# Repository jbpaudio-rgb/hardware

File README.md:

# Octavio Synth — synthé matériel

Un synthé de table à 4 parties : Raspberry Pi 5, carte HAT audio, façade RP2040 (9 encodeurs, 14 boutons, LED), écran tactile 5 po, boîtier imprimé en 3D. Il fait tourner les moteurs des plugins Octavio (MINI, PRO70, A26, J8, CS8, VC3, M20, EASEL, VACT), plus DX7, DFAM, DR8, SAMPLER et LINE IN.

## Où trouver quoi

| Dossier | Contenu |
| --- | --- |
| `box/cartes/facade` | Carte de façade (KiCad), Gerbers, BOM et CPL pour JLCPCB : `octavio-facade-gerbers-jlcpcb.zip`, `jlcpcb-bom.csv`, `jlcpcb-cpl.csv` |
| `box/cartes/hat` | Carte HAT audio (KiCad), Gerbers, BOM et CPL pour JLCPCB |
| `box/enclosure` | Boîtier : fichiers STL à imprimer, guide de montage 3D (`guide-montage.html`), aperçu 3D, liste de quincaillerie (`LISEZMOI.md`) |
| `box/facade-fw` | Micrologiciel du RP2040 de la façade |
| `box/systeme` | Installation sur le Pi : services, transfert de fichiers par USB-C |
| `box/web` | Simulateur dans le navigateur (`octavio-box.html`) |
| `box/` | Le programme du synthé (C++) : `Box.h`, `Panel.h`, `ui/`, `main.cpp` |
| `core/` | Les moteurs de son et les effets, partagés avec les plugins |

Le détail du programme est dans [`box/README.md`](box/README.md).

## Compiler

```
cmake -S box -B build -DCMAKE_BUILD_TYPE=Release
cmake --build build -j
```

Sur le Raspberry Pi, il faut ALSA et SDL2 (`sudo apt install libasound2-dev libsdl2-dev`). Sans carte son ni écran : `-DOCTAVIO_NO_DEVICES=ON`.

Le simulateur : `WASI_SDK=/chemin/vers/wasi-sdk bash box/web/build.sh`.

## Commander les cartes

Dans chaque dossier de carte : le zip de Gerbers, `jlcpcb-bom.csv` et `jlcpcb-cpl.csv`. Chez JLCPCB : 4 couches, 1,6 mm, assemblage Standard côté Top. Les étapes sont dans le `LISEZMOI.md` de chaque carte.

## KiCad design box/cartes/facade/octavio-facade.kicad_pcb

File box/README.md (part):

# Octavio Box

The program of the Octavio hardware synth: a 4-part multitimbral synth. Each part has one of the 11 Octavio engines
(`core/synth`), its own 8-slot FX rack (`core/FxEngine.h`) and its own MIDI channel; plus a mixer, MIDI in and a
shared tempo. It uses the plugins' C++ engines
as they are (no JUCE), with [RtAudio](https://github.com/thestk/rtaudio) and [RtMidi](https://github.com/thestk/rtmidi)
for the audio and MIDI devices (`third_party/`, MIT-style licences).

It runs the same on a Mac (to try it now) and on a Raspberry Pi 5 / CM5 (the hardware). Until the front panel exists,
it is driven by commands typed in the terminal; the panel will send the same commands.

## Build and run

Mac (needs the Xcode command line tools and CMake: `xcode-select --install`, `brew install cmake`):

```
cmake -S box -B build-box
cmake --build build-box
./build-box/octavio-box
```

Raspberry Pi OS: `sudo apt install cmake g++ libasound2-dev`, then the same three lines. Or all at once (packages, code in `~/hardware`, build, screen lines in `config.txt`, services that start at power-on): `curl -sL https://raw.githubusercontent.com/jbpaudio-rgb/hardware/main/box/systeme/installer.sh | bash`, then `sudo reboot`.

Options: `--buffer 128` (samples per block), `--rate 48000`, `--device n` (see `devices`), `--script file`
(commands run at start, for example a saved state).

## Playing it

- Parts start as MINI, PRO70, VACT and DR8 on MIDI channels 1-4. `chan` changes a part's channel; two parts on the
  same channel play together (a layer). A channel no part listens to plays the selected part.
- Every MIDI input and output is opened (looked for again every 2 s), plus virtual ports "Octavio Box" for a DAW. A port
  named after a Bluetooth device BlueZ knows (`bluetoothctl devices`) counts as Bluetooth (BLE MIDI: BlueZ built with
  MIDI support), the others as USB.
- CCs follow the plugin and the app: each engine's controls on CC 2-5, 7-31, 70-95, 102-119, 33-63 (see `params`).
  Any control (and any switch) can be given a CC by MIDI learn: a long press on it on the screen, then move a knob of
  the MIDI controller (on the part's channel). A learnt CC goes before the default one; it is saved in the multi
  (`cc <n> <engine> <control>`), and the screen shows it under the control.
- Tempo and sync (TEMPO & SYNC page, or `sync`): the clock is internal or follows MIDI clock from DIN MIDI, USB or
  Bluetooth; start / stop received or not; MIDI clock (and start / stop) sent to DIN, USB and / or Bluetooth; DIN MIDI
  thru on or off; a multi loads its tempo or not. Kept in `~/octavio/reglages.txt`.
- Type `help` for the commands. Example:

```
p 2              part 2
eng cs8          CS8 on it
params cutoff    its controls whose name has CUTOFF
set cutoff 0.7
fx slot          the FX slots
fxset slot0 7    reverb in slot 1 (0 = off, 1-16 = OVERDRIVE ... SHIMMER)
note 60 .8 500   play a note
bpm 100
play
status           engines, levels, CPU
chan 5           part 2 now listens to MIDI channel 5
savepart pad.txt this part's sound (p 4, then load pad.txt, copies it to part 4)
save live.txt    all 4 parts, as commands (load live.txt or --script live.txt)
```

## The screen

`ui/Screen.h` draws the synth's screen (Raspberry Pi Touch Display 2, 5", used in landscape: 1280 x 720), in a sober
hardware style: the page's title at the top, in the selected part's colour (the 1-4 buttons change the part), with
in its right corner the output's waveform (tap it: a tuner for the selected part), the tempo with its clock source
(tap it: TEMPO & SYNC) and a play / stop button; then the page chosen with the panel's page buttons. The 8 controls of a page sit 2 x 4 like the 8 encoders to
the right of the screen, each with a ring like the encoder's LED ring; a control that just moved lights up in the part's
colour. The pages are described below (front panel).

Touch: tap a part to select it, drag a control up or down to change it (double-tap = default value), tap the play button
to start / stop, on PRESETS (MIXER's tabs) tap a sound or a multi to pick it and tap it again to load it. The screen goes through the same logic as
the front panel (`Panel.h`), so the knobs, the buttons and the touch screen always agree.

It is drawn in software (`ui/Canvas.h`, about 2 ms per picture on a desktop CPU) and shown:
- on the Pi, straight on the display through KMS (no desktop needed): `--rotate 90` or `--rotate 270` turns the
  picture for the portrait panel (try the other one if it is upside down); the touch panel is read from `/dev/input`.
  `config.txt` needs `dtoverlay=vc4-kms-v3d` and `dtoverlay=vc4-kms-dsi-ili9881-5inch`; the user running octavio-box
  needs the `video` and `input` groups;
- on a computer, in a window when SDL2 is installed (`brew install sdl2`, `apt install libsdl2-dev`), `--zoom 0.75`
  for a smaller window. Keys stand in for the panel: 1-4 parts, `e v b f t m q x i p` pages, `[` `]` knob 9, space play.

`--no-screen` runs without it; `shot file.png` saves a picture of it (also in `--render`, for tests), `touch x y dy`
plays a finger, `page`, `knob` and `push` play the front panel from the terminal. With a screen, the synth keeps running
when the terminal closes (as a service). Fonts: DejaVu Sans Condensed (`third_party/fonts`, free licence).

## In a web browser

`box/web/` builds the same program for the browser (`WASI_SDK=/path/to/wasi-sdk box/web/build.sh`): the synth, the
panel's logic and the screen are compiled to WebAssembly (`boxwasm.cpp`) and `octavio-box.html` is one self-contained
page with the front panel around the screen. The sound runs in an AudioWorklet; the page keeps a copy of the synth for
the panel and the screen and posts each change to it. The virtual panel speaks the real panel's USB-MIDI protocol and
lights its rings the way the panel firmware does. Encoders: drag or wheel, click = push. Notes: the computer keyboard,
the keys under the panel or any Web MIDI input. Multis are kept in the browser.

## Offline render (no devices)

`octavio-box --render out.wav < script.txt` runs the commands of a script, where `wait <ms>` renders that much sound,
and writes a WAV. Build it alone with `-DOCTAVIO_NO_DEVICES=ON` (no audio library needed).

## Measured load

On one core of an Intel Xeon at 2.1 GHz (test server): 4 parts (J8, PRO70 and CS8 replaying 6-note chords, DR8
playing), each with 8 effects (reverb, shimmer, granular, delay, phaser, chorus, tape, overdrive) = about 29 % of one
core, 16 MB of memory. To be measured again on a Raspberry Pi 5.

## On the hardware synth (Raspberry Pi 5 + Octavio HAT + front panel)
`/boot/firmware/config.txt`:
```
dtoverlay=hifiberry-dacplusadcpro
dtoverlay=uart2-pi5
```
Then `octavio-box --device <n>` with the HiFiBerry card (see `devices`). On start it also:
- opens DIN MIDI on `/dev/ttyAMA2` at 31250 baud (`--serial` to change). MIDI IN plays like any other input; everything is echoed to MIDI OUT (thru);
- switches the headphone amplifier on (`--phones 0-63`, default 48; `phones` command while running);
- looks for the front panel ("Octavio Facade" USB-MIDI) every 2 s, so it can be plugged in at any time.

Files over USB (`systeme/`): `sudo sh systeme/usb-gadget.sh` once makes the Pi 5's USB-C port a USB device when a
computer is plugged into it (an Ethernet gadget; the box is 10.55.0.1 and `octavio.local`) and starts
`systeme/transfert.py`, a page at http://octavio.local: the multis (download one or all as a zip, upload, delete) and
the SAMPLER's WAV files (drag and drop files or whole folders, download, delete), straight on the SD card; the box
sees them at once. It answers only on the USB link. The screen says when a computer is connected. The computer then
powers the box through that port: it must give 3 A (most laptops' USB-C ports do), or a powered USB-C hub goes
between them. Adjust the user and paths in `systeme/octavio-transfert.service` if the box's user is not `octavio`.

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
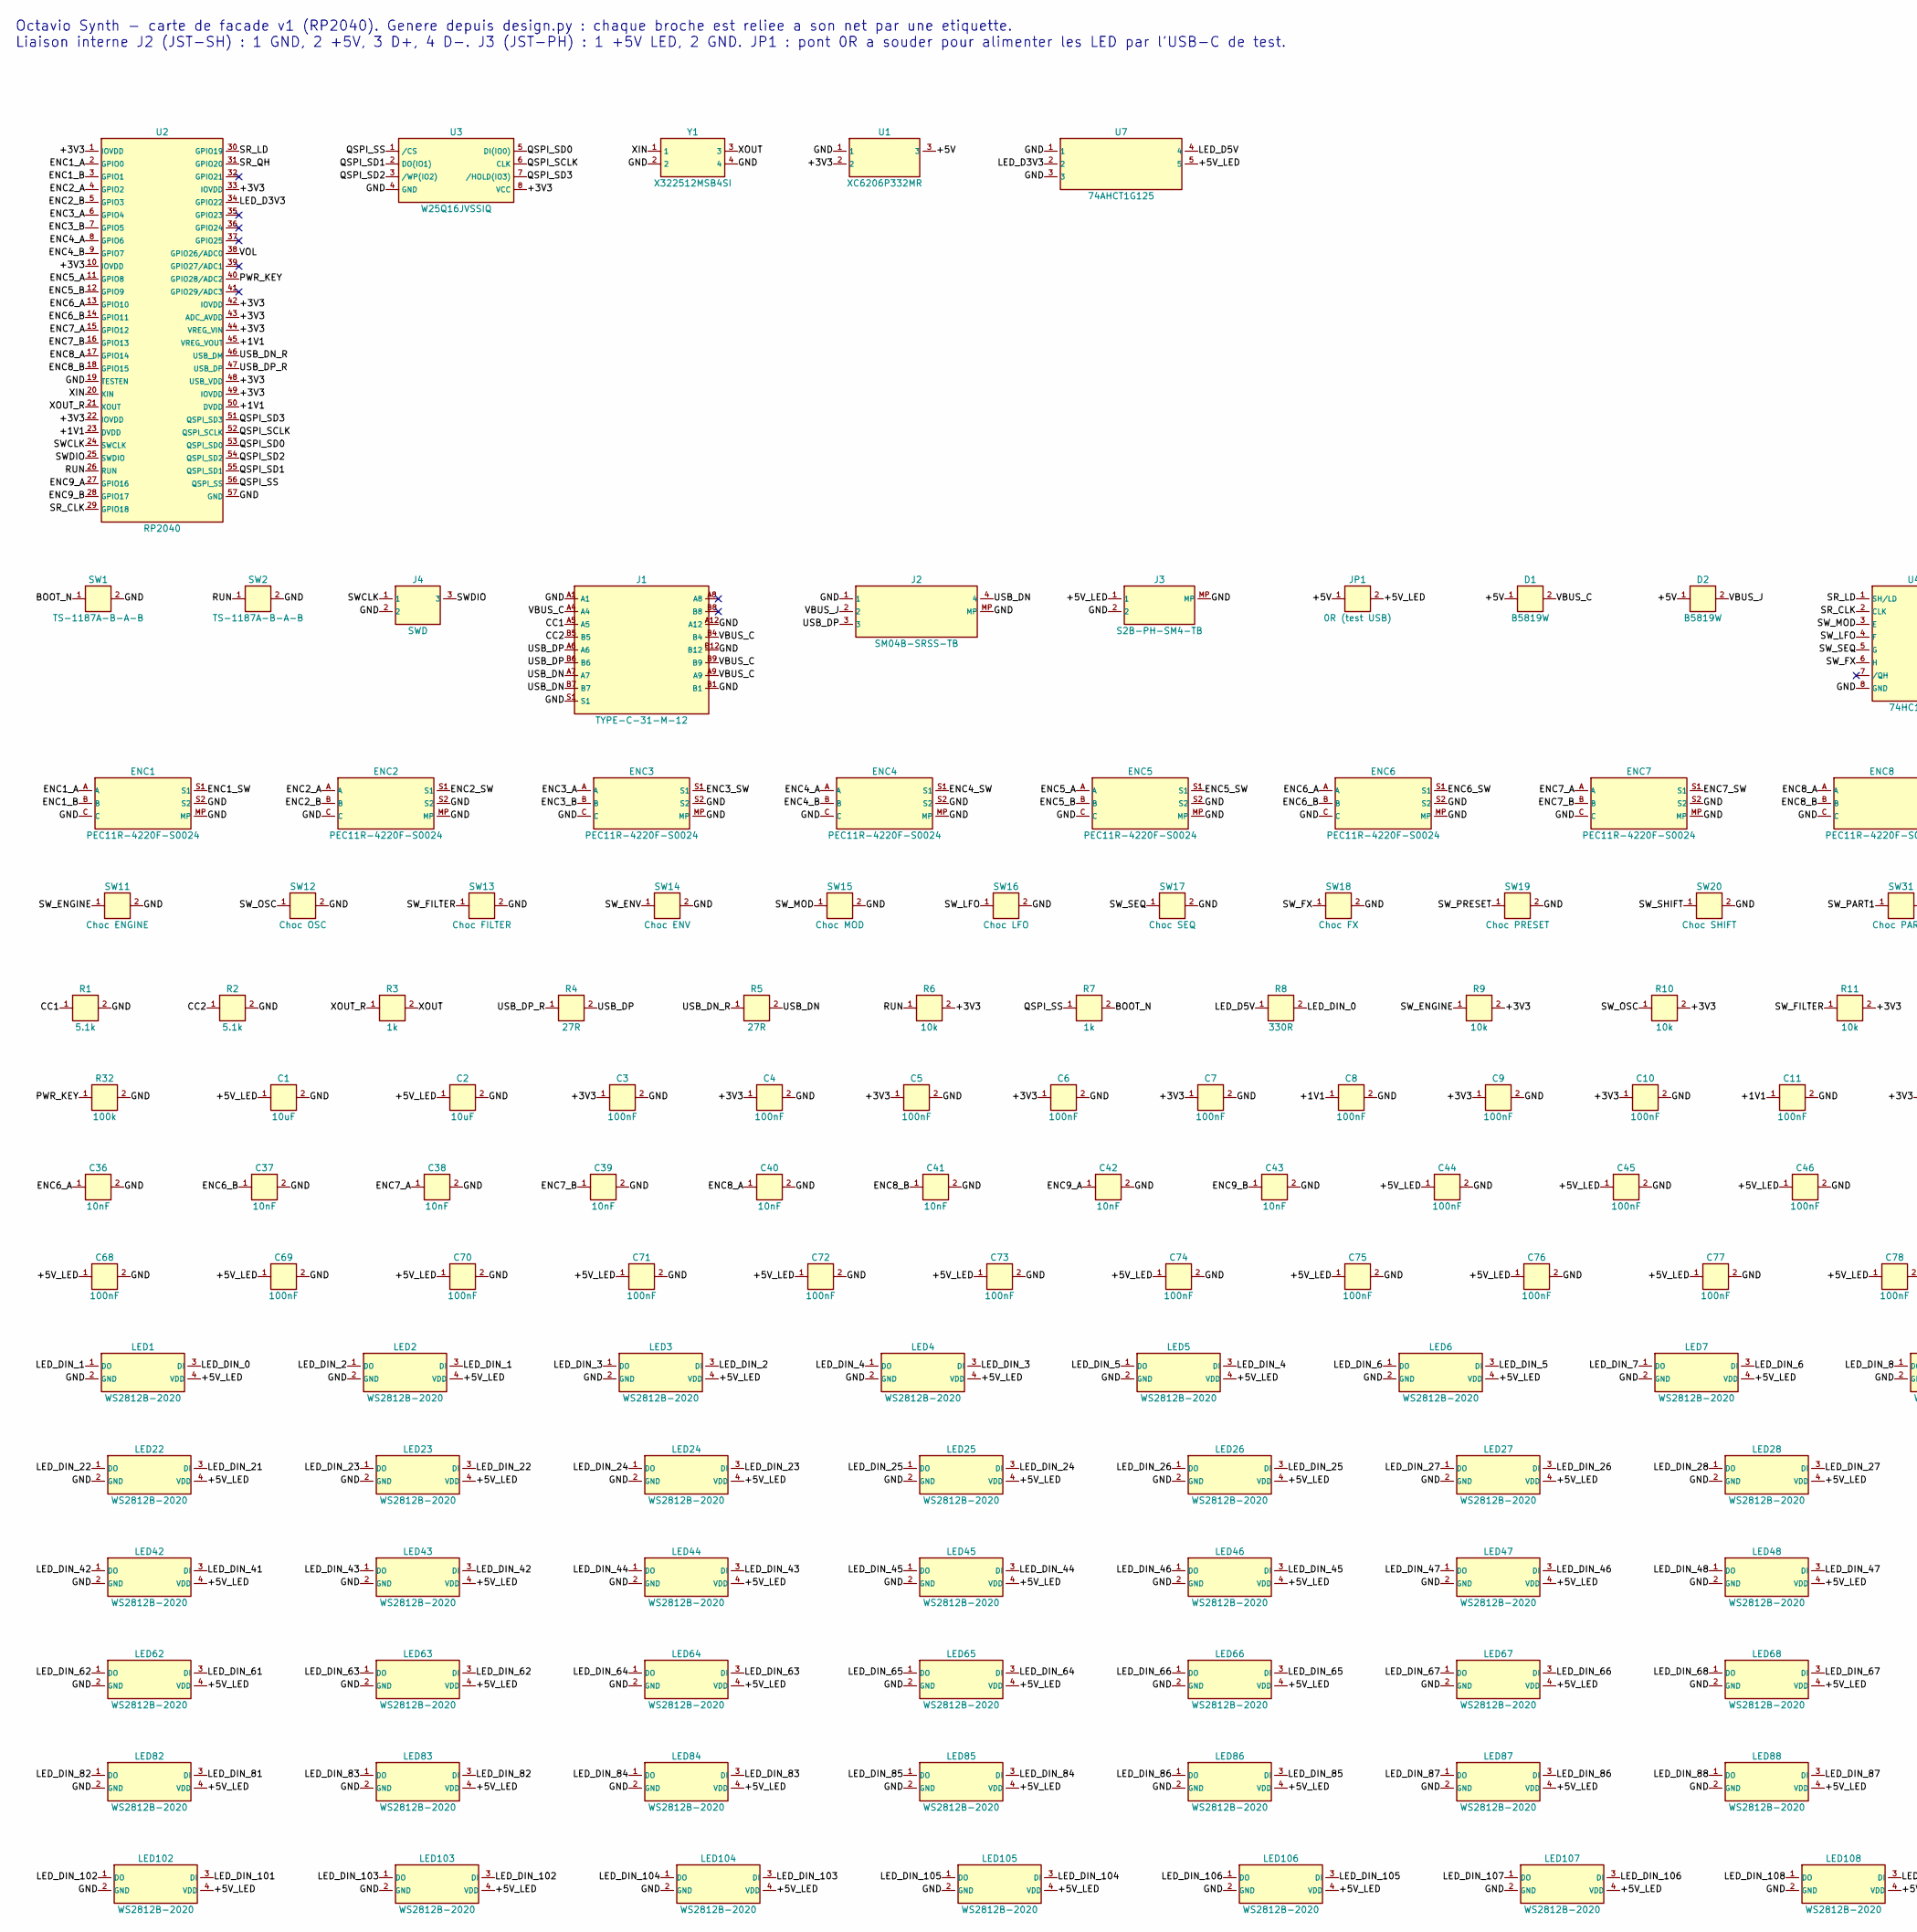
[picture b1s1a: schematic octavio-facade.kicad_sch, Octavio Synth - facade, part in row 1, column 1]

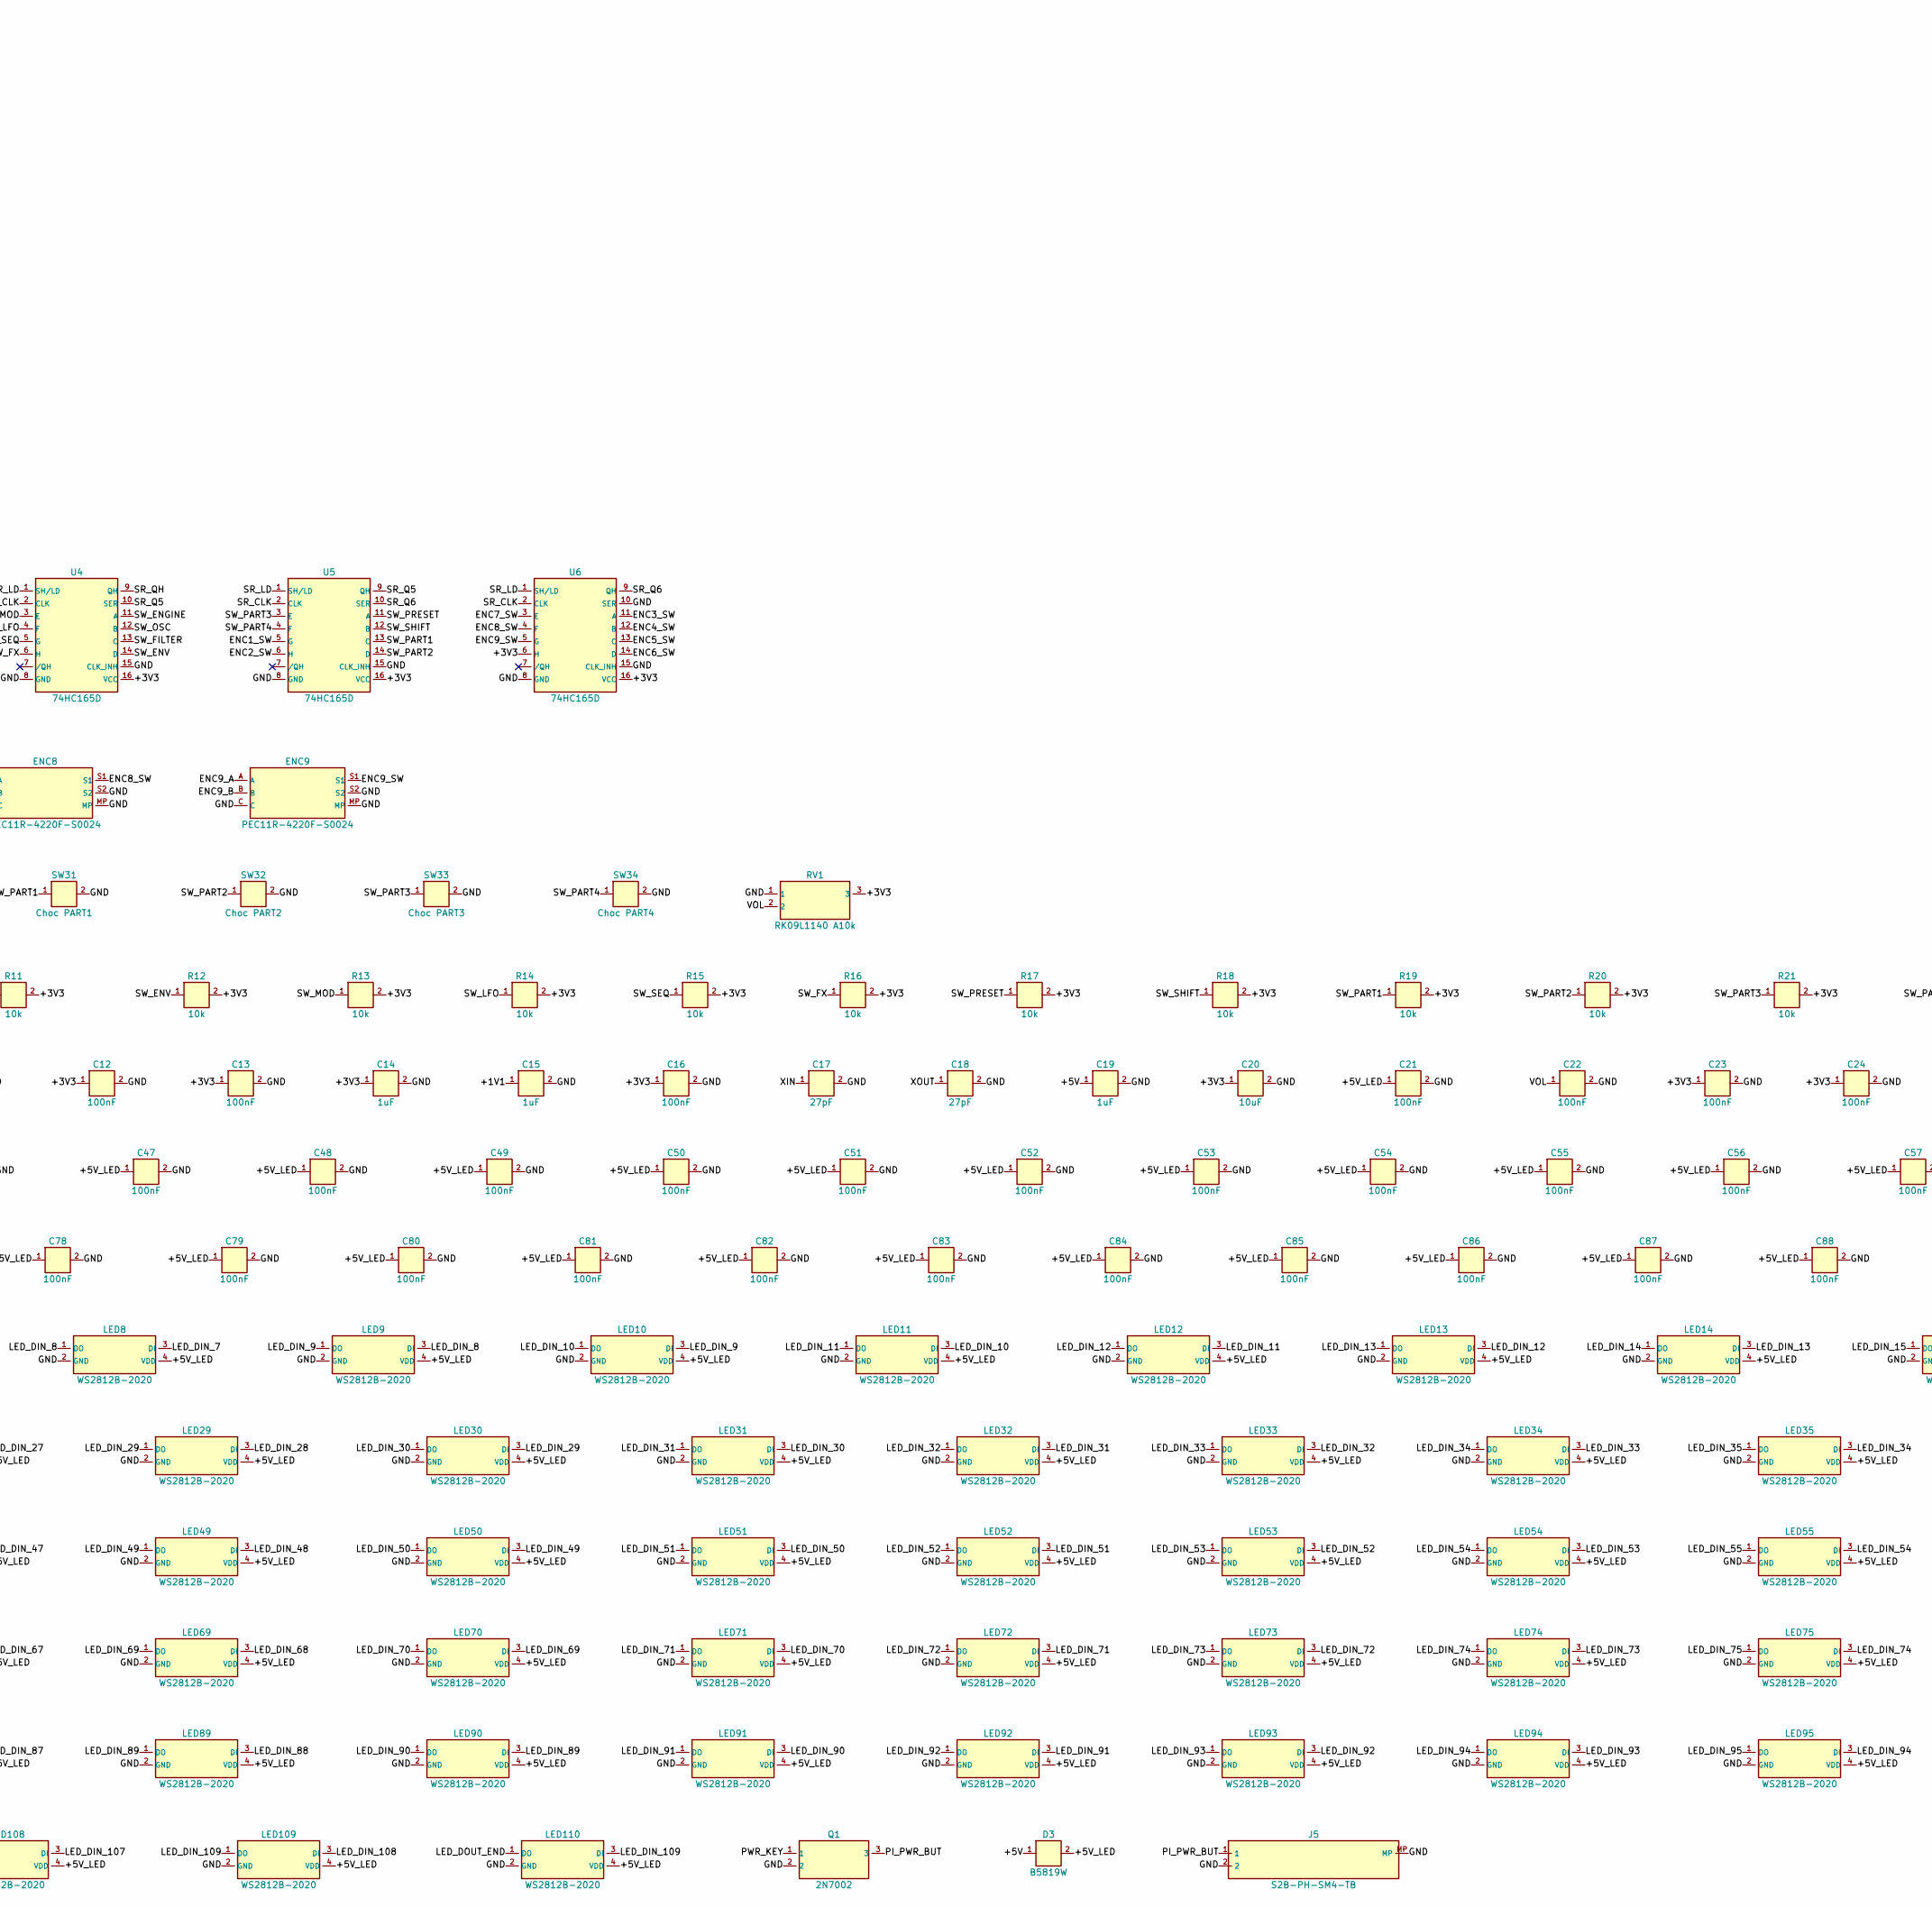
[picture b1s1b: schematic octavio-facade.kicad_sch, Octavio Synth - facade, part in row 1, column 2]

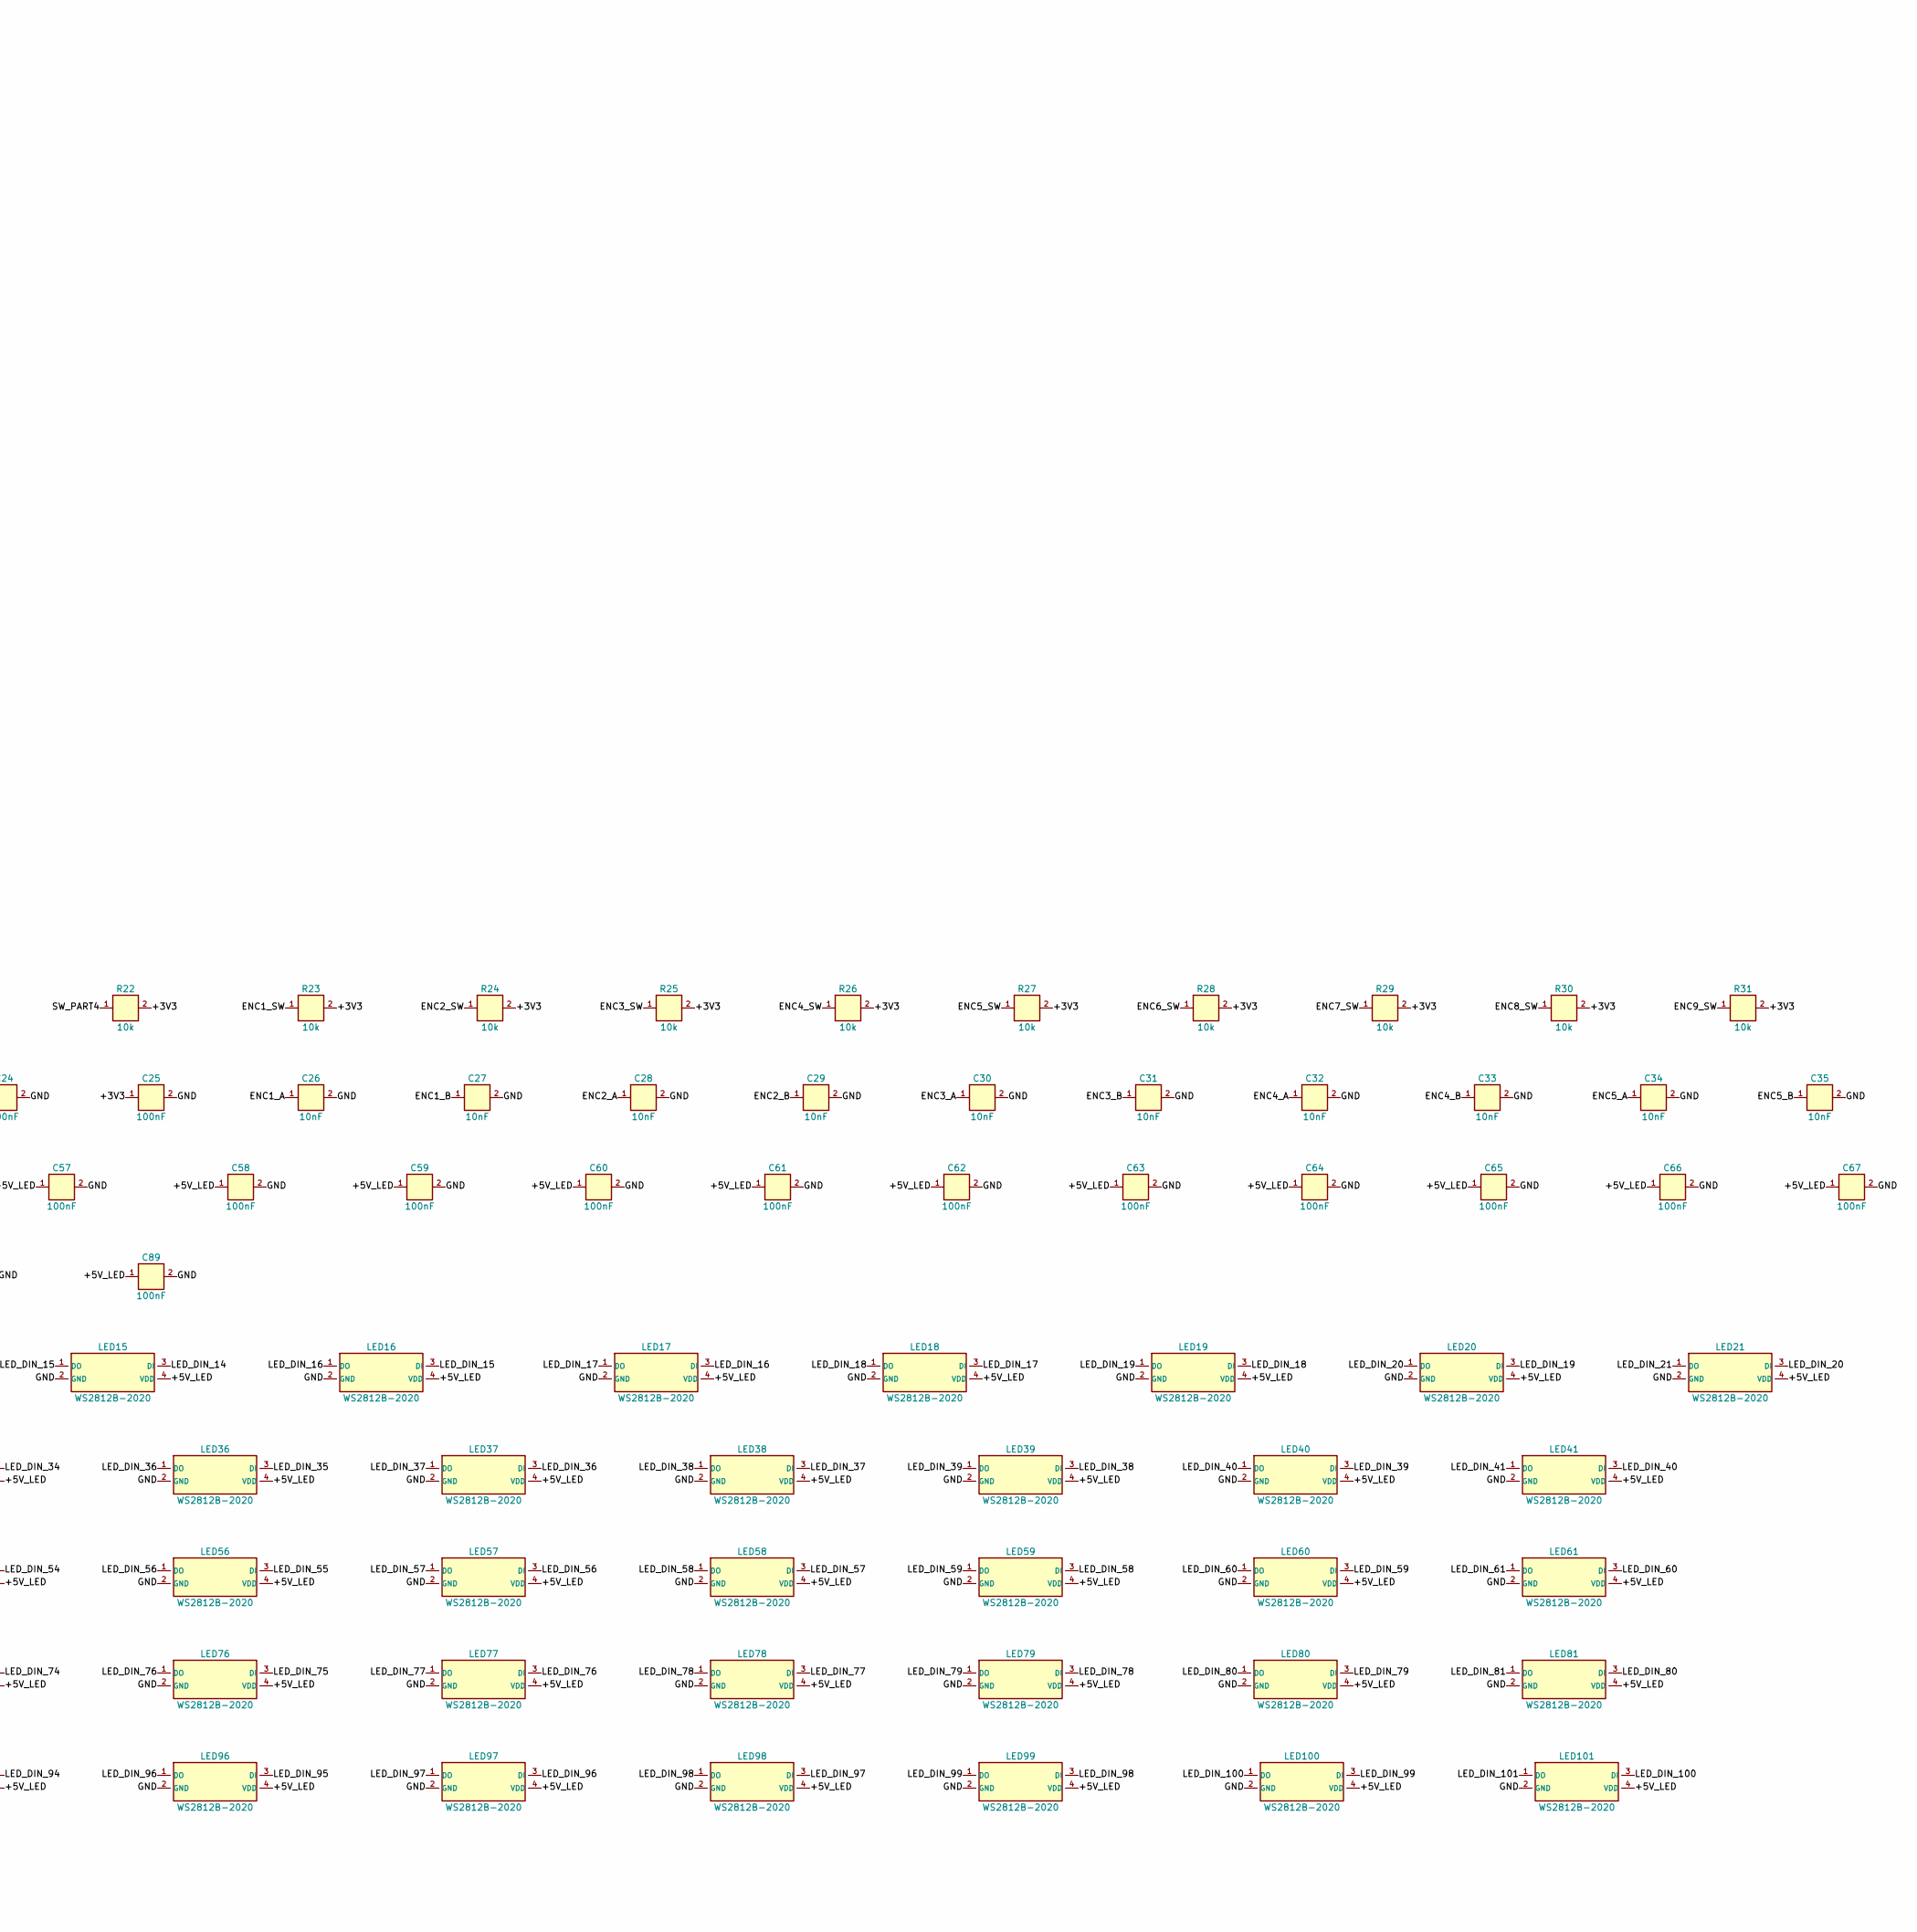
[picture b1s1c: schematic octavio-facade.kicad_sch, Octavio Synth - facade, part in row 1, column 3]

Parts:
C1, C2, C20: 10uF; C_0603_1608Metric; LCSC C19702
C3, C4, C5, C6, C7, C8, C9, C10, C11, C12, C13, C16, C21, C22, C23, C24, C25, C44, C45, C46, C47, C48, C49, C50, C51, C52, C53, C54, C55, C56, C57, C58, C59, C60, C61, C62, C63, C64, C65, C66, C67, C68, C69, C70, C71, C72, C73, C74, C75, C76, C77, C78, C79, C80, C81, C82, C83, C84, C85, C86, C87, C88, C89: 100nF; C_0402_1005Metric; LCSC C1525
C14, C15, C19: 1uF; C_0402_1005Metric; LCSC C52923
C17, C18: 27pF; C_0402_1005Metric; LCSC C1557
C26, C27, C28, C29, C30, C31, C32, C33, C34, C35, C36, C37, C38, C39, C40, C41, C42, C43: 10nF; C_0402_1005Metric; LCSC C15195
D1, D2, D3: B5819W; D_SOD-123; LCSC C8598
ENC1, ENC2, ENC3, ENC4, ENC5, ENC6, ENC7, ENC8, ENC9: PEC11R-4220F-S0024; RotaryEncoder_Alps_EC11E-Switch_Vertical_H20mm; LCSC C143797
J1: TYPE-C-31-M-12; USB_C_Receptacle_HRO_TYPE-C-31-M-12; LCSC C165948
J2: SM04B-SRSS-TB; JST_SH_SM04B-SRSS-TB_1x04-1MP_P1.00mm_Horizontal; LCSC C160404
J3, J5: S2B-PH-SM4-TB; JST_PH_S2B-PH-SM4-TB_1x02-1MP_P2.00mm_Horizontal; LCSC C295747
J4: SWD; PinHeader_1x03_P2.54mm_Vertical
JP1: 0R (test USB); R_0603_1608Metric
LED1, LED2, LED3, LED4, LED5, LED6, LED7, LED8, LED9, LED10, LED11, LED12, LED13, LED14, LED15, LED16, LED17, LED18, LED19, LED20, LED21, LED22, LED23, LED24, LED25, LED26, LED27, LED28, LED29, LED30, LED31, LED32, LED33, LED34, LED35, LED36, LED37, LED38, LED39, LED40, LED41, LED42, LED43, LED44, LED45, LED46, LED47, LED48, LED49, LED50, LED51, LED52, LED53, LED54, LED55, LED56, LED57, LED58, LED59, LED60, LED61, LED62, LED63, LED64, LED65, LED66, LED67, LED68, LED69, LED70, LED71, LED72, LED73, LED74, LED75, LED76, LED77, LED78, LED79, LED80, LED81, LED82, LED83, LED84, LED85, LED86, LED87, LED88, LED89, LED90, LED91, LED92, LED93, LED94, LED95, LED96, LED97, LED98, LED99, LED100, LED101, LED102, LED103, LED104, LED105, LED106, LED107, LED108, LED109, LED110: WS2812B-2020; LED_WS2812B-2020; LCSC C965555
Q1: 2N7002; SOT-23; LCSC C8545
R1, R2: 5.1k; R_0402_1005Metric; LCSC C25905
R3, R7: 1k; R_0402_1005Metric; LCSC C11702
R4, R5: 27R; R_0402_1005Metric; LCSC C25100
R6, R9, R10, R11, R12, R13, R14, R15, R16, R17, R18, R19, R20, R21, R22, R23, R24, R25, R26, R27, R28, R29, R30, R31: 10k; R_0402_1005Metric; LCSC C25744
R8: 330R; R_0402_1005Metric; LCSC C25104
R32: 100k; R_0402_1005Metric; LCSC C25741
RV1: RK09L1140 A10k; Potentiometer_Alps_RK09L_Single_Vertical; LCSC C470448
SW1, SW2: TS-1187A-B-A-B; SW_SPST_SKQG_WithoutStem; LCSC C318884
SW11: Choc ENGINE; SW_Kailh_Choc_V1_1.00u; LCSC C400229
SW12: Choc OSC; SW_Kailh_Choc_V1_1.00u; LCSC C400229
SW13: Choc FILTER; SW_Kailh_Choc_V1_1.00u; LCSC C400229
SW14: Choc ENV; SW_Kailh_Choc_V1_1.00u; LCSC C400229
SW15: Choc MOD; SW_Kailh_Choc_V1_1.00u; LCSC C400229
SW16: Choc LFO; SW_Kailh_Choc_V1_1.00u; LCSC C400229
SW17: Choc SEQ; SW_Kailh_Choc_V1_1.00u; LCSC C400229
SW18: Choc FX; SW_Kailh_Choc_V1_1.00u; LCSC C400229
SW19: Choc PRESET; SW_Kailh_Choc_V1_1.00u; LCSC C400229
SW20: Choc SHIFT; SW_Kailh_Choc_V1_1.00u; LCSC C400229
SW31: Choc PART1; SW_Kailh_Choc_V1_1.00u; LCSC C400229
SW32: Choc PART2; SW_Kailh_Choc_V1_1.00u; LCSC C400229
SW33: Choc PART3; SW_Kailh_Choc_V1_1.00u; LCSC C400229
SW34: Choc PART4; SW_Kailh_Choc_V1_1.00u; LCSC C400229
U1: XC6206P332MR; SOT-23; LCSC C5446
U2: RP2040; RP2040-QFN-56; LCSC C2040
U3: W25Q16JVSSIQ; SOIC-8_5.23x5.23mm_P1.27mm; LCSC C131025
U4, U5, U6: 74HC165D; SOIC-16_3.9x9.9mm_P1.27mm; LCSC C5613
U7: 74AHCT1G125; SOT-353_SC-70-5; LCSC C12495
Y1: X322512MSB4SI; Crystal_SMD_3225-4Pin_3.2x2.5mm; LCSC C9002

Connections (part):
+1V1: C8.1, C11.1, C15.1, U2.23 (DVDD), U2.45 (VREG_VOUT), U2.50 (DVDD)
+3V3: C3.1, C4.1, C5.1, C6.1, C7.1, C9.1, C10.1, C12.1, C13.1, C14.1, C16.1, C20.1, C23.1, C24.1, C25.1, R6.2, R9.2, R10.2, R11.2, R12.2, R13.2, R14.2, R15.2, R16.2, R17.2, R18.2, R19.2, R20.2, R21.2, R22.2, R23.2, R24.2, R25.2, R26.2, R27.2, R28.2, R29.2, R30.2, R31.2, RV1.3, U1.2, U2.1 (IOVDD), U2.10 (IOVDD), U2.22 (IOVDD), U2.33 (IOVDD), U2.42 (IOVDD), U2.43 (ADC_AVDD), U2.44 (VREG_VIN), U2.48 (USB_VDD), U2.49 (IOVDD), U3.8 (VCC), U4.16 (VCC), U5.16 (VCC), U6.6 (H), U6.16 (VCC)
+5V: C19.1, D1.1, D2.1, D3.1, JP1.1, U1.3
+5V_LED: C1.1, C2.1, C21.1, C44.1, C45.1, C46.1, C47.1, C48.1, C49.1, C50.1, C51.1, C52.1, C53.1, C54.1, C55.1, C56.1, C57.1, C58.1, C59.1, C60.1, C61.1, C62.1, C63.1, C64.1, C65.1, C66.1, C67.1, C68.1, C69.1, C70.1, C71.1, C72.1, C73.1, C74.1, C75.1, C76.1, C77.1, C78.1, C79.1, C80.1, C81.1, C82.1, C83.1, C84.1, C85.1, C86.1, C87.1, C88.1, C89.1, D3.2, J3.1, JP1.2, LED1.4 (VDD), LED2.4 (VDD), LED3.4 (VDD), LED4.4 (VDD), LED5.4 (VDD), LED6.4 (VDD), LED7.4 (VDD), LED8.4 (VDD), LED9.4 (VDD), LED10.4 (VDD), LED11.4 (VDD), LED12.4 (VDD), LED13.4 (VDD), LED14.4 (VDD), LED15.4 (VDD), LED16.4 (VDD), LED17.4 (VDD), LED18.4 (VDD), LED19.4 (VDD), LED20.4 (VDD), LED21.4 (VDD), LED22.4 (VDD), LED23.4 (VDD), LED24.4 (VDD), LED25.4 (VDD), LED26.4 (VDD), LED27.4 (VDD), LED28.4 (VDD)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
BOOT_N: R7.2, SW1.1
CC1: J1.A5, R1.1
CC2: J1.B5, R2.1
ENC1_A: C26.1, ENC1.A, U2.2 (GPIO0)
ENC1_B: C27.1, ENC1.B, U2.3 (GPIO1)
ENC1_SW: ENC1.S1, R23.1, U5.5 (G)
ENC2_A: C28.1, ENC2.A, U2.4 (GPIO2)
ENC2_B: C29.1, ENC2.B, U2.5 (GPIO3)
ENC2_SW: ENC2.S1, R24.1, U5.6 (H)
ENC3_A: C30.1, ENC3.A, U2.6 (GPIO4)
ENC3_B: C31.1, ENC3.B, U2.7 (GPIO5)
ENC3_SW: ENC3.S1, R25.1, U6.11 (A)
ENC4_A: C32.1, ENC4.A, U2.8 (GPIO6)
ENC4_B: C33.1, ENC4.B, U2.9 (GPIO7)
ENC4_SW: ENC4.S1, R26.1, U6.12 (B)
ENC5_A: C34.1, ENC5.A, U2.11 (GPIO8)
ENC5_B: C35.1, ENC5.B, U2.12 (GPIO9)
ENC5_SW: ENC5.S1, R27.1, U6.13 (C)
ENC6_A: C36.1, ENC6.A, U2.13 (GPIO10)
ENC6_B: C37.1, ENC6.B, U2.14 (GPIO11)
ENC6_SW: ENC6.S1, R28.1, U6.14 (D)
ENC7_A: C38.1, ENC7.A, U2.15 (GPIO12)
ENC7_B: C39.1, ENC7.B, U2.16 (GPIO13)
ENC7_SW: ENC7.S1, R29.1, U6.3 (E)
ENC8_A: C40.1, ENC8.A, U2.17 (GPIO14)
ENC8_B: C41.1, ENC8.B, U2.18 (GPIO15)
ENC8_SW: ENC8.S1, R30.1, U6.4 (F)
ENC9_A: C42.1, ENC9.A, U2.27 (GPIO16)
ENC9_B: C43.1, ENC9.B, U2.28 (GPIO17)
ENC9_SW: ENC9.S1, R31.1, U6.5 (G)
GND: C1.2, C2.2, C3.2, C4.2, C5.2, C6.2, C7.2, C8.2, C9.2, C10.2, C11.2, C12.2, C13.2, C14.2, C15.2, C16.2, C17.2, C18.2, C19.2, C20.2, C21.2, C22.2, C23.2, C24.2, C25.2, C26.2, C27.2, C28.2, C29.2, C30.2, C31.2, C32.2, C33.2, C34.2, C35.2, C36.2, C37.2, C38.2, C39.2, C40.2, C41.2, C42.2, C43.2, C44.2, C45.2, C46.2, C47.2, C48.2, C49.2, C50.2, C51.2, C52.2, C53.2, C54.2, C55.2, C56.2, C57.2, C58.2, C59.2, C60.2, C61.2, C62.2, C63.2, C64.2, C65.2, C66.2, C67.2, C68.2, C69.2, C70.2, C71.2, C72.2, C73.2, C74.2, C75.2, C76.2, C77.2, C78.2, C79.2, C80.2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
LED_D3V3: U2.34 (GPIO22), U7.2
LED_D5V: R8.1, U7.4
LED_DIN_0: LED1.3 (DI), R8.2
LED_DIN_1: LED1.1 (DO), LED2.3 (DI)
LED_DIN_2: LED2.1 (DO), LED3.3 (DI)
LED_DIN_3: LED3.1 (DO), LED4.3 (DI)
LED_DIN_4: LED4.1 (DO), LED5.3 (DI)
LED_DIN_5: LED5.1 (DO), LED6.3 (DI)
LED_DIN_6: LED6.1 (DO), LED7.3 (DI)
LED_DIN_7: LED7.1 (DO), LED8.3 (DI)
LED_DIN_8: LED8.1 (DO), LED9.3 (DI)
LED_DIN_9: LED9.1 (DO), LED10.3 (DI)
LED_DIN_10: LED10.1 (DO), LED11.3 (DI)
LED_DIN_11: LED11.1 (DO), LED12.3 (DI)
LED_DIN_12: LED12.1 (DO), LED13.3 (DI)
LED_DIN_13: LED13.1 (DO), LED14.3 (DI)
LED_DIN_14: LED14.1 (DO), LED15.3 (DI)
LED_DIN_15: LED15.1 (DO), LED16.3 (DI)
LED_DIN_16: LED16.1 (DO), LED17.3 (DI)
LED_DIN_17: LED17.1 (DO), LED18.3 (DI)
LED_DIN_18: LED18.1 (DO), LED19.3 (DI)
LED_DIN_19: LED19.1 (DO), LED20.3 (DI)
LED_DIN_20: LED20.1 (DO), LED21.3 (DI)
LED_DIN_21: LED21.1 (DO), LED22.3 (DI)
LED_DIN_22: LED22.1 (DO), LED23.3 (DI)
LED_DIN_23: LED23.1 (DO), LED24.3 (DI)
LED_DIN_24: LED24.1 (DO), LED25.3 (DI)
LED_DIN_25: LED25.1 (DO), LED26.3 (DI)
LED_DIN_26: LED26.1 (DO), LED27.3 (DI)
LED_DIN_27: LED27.1 (DO), LED28.3 (DI)
LED_DIN_28: LED28.1 (DO), LED29.3 (DI)
LED_DIN_29: LED29.1 (DO), LED30.3 (DI)
LED_DIN_30: LED30.1 (DO), LED31.3 (DI)
LED_DIN_31: LED31.1 (DO), LED32.3 (DI)
LED_DIN_32: LED32.1 (DO), LED33.3 (DI)
LED_DIN_33: LED33.1 (DO), LED34.3 (DI)
LED_DIN_34: LED34.1 (DO), LED35.3 (DI)
LED_DIN_35: LED35.1 (DO), LED36.3 (DI)
LED_DIN_36: LED36.1 (DO), LED37.3 (DI)
LED_DIN_37: LED37.1 (DO), LED38.3 (DI)
LED_DIN_38: LED38.1 (DO), LED39.3 (DI)
LED_DIN_39: LED39.1 (DO), LED40.3 (DI)
LED_DIN_40: LED40.1 (DO), LED41.3 (DI)
LED_DIN_41: LED41.1 (DO), LED42.3 (DI)
LED_DIN_42: LED42.1 (DO), LED43.3 (DI)
LED_DIN_43: LED43.1 (DO), LED44.3 (DI)
LED_DIN_44: LED44.1 (DO), LED45.3 (DI)
LED_DIN_45: LED45.1 (DO), LED46.3 (DI)
LED_DIN_46: LED46.1 (DO), LED47.3 (DI)
LED_DIN_47: LED47.1 (DO), LED48.3 (DI)
LED_DIN_48: LED48.1 (DO), LED49.3 (DI)
LED_DIN_49: LED49.1 (DO), LED50.3 (DI)
LED_DIN_50: LED50.1 (DO), LED51.3 (DI)
LED_DIN_51: LED51.1 (DO), LED52.3 (DI)
LED_DIN_52: LED52.1 (DO), LED53.3 (DI)
LED_DIN_53: LED53.1 (DO), LED54.3 (DI)
LED_DIN_54: LED54.1 (DO), LED55.3 (DI)
LED_DIN_55: LED55.1 (DO), LED56.3 (DI)
LED_DIN_56: LED56.1 (DO), LED57.3 (DI)
LED_DIN_57: LED57.1 (DO), LED58.3 (DI)
LED_DIN_58: LED58.1 (DO), LED59.3 (DI)
LED_DIN_59: LED59.1 (DO), LED60.3 (DI)
LED_DIN_60: LED60.1 (DO), LED61.3 (DI)
LED_DIN_61: LED61.1 (DO), LED62.3 (DI)
LED_DIN_62: LED62.1 (DO), LED63.3 (DI)
LED_DIN_63: LED63.1 (DO), LED64.3 (DI)
LED_DIN_64: LED64.1 (DO), LED65.3 (DI)
LED_DIN_65: LED65.1 (DO), LED66.3 (DI)
LED_DIN_66: LED66.1 (DO), LED67.3 (DI)
LED_DIN_67: LED67.1 (DO), LED68.3 (DI)
LED_DIN_68: LED68.1 (DO), LED69.3 (DI)
LED_DIN_69: LED69.1 (DO), LED70.3 (DI)
LED_DIN_70: LED70.1 (DO), LED71.3 (DI)
LED_DIN_71: LED71.1 (DO), LED72.3 (DI)
LED_DIN_72: LED72.1 (DO), LED73.3 (DI)
LED_DIN_73: LED73.1 (DO), LED74.3 (DI)
LED_DIN_74: LED74.1 (DO), LED75.3 (DI)
LED_DIN_75: LED75.1 (DO), LED76.3 (DI)
LED_DIN_76: LED76.1 (DO), LED77.3 (DI)
LED_DIN_77: LED77.1 (DO), LED78.3 (DI)
LED_DIN_78: LED78.1 (DO), LED79.3 (DI)
LED_DIN_79: LED79.1 (DO), LED80.3 (DI)
LED_DIN_80: LED80.1 (DO), LED81.3 (DI)
LED_DIN_81: LED81.1 (DO), LED82.3 (DI)
LED_DIN_82: LED82.1 (DO), LED83.3 (DI)
LED_DIN_83: LED83.1 (DO), LED84.3 (DI)
LED_DIN_84: LED84.1 (DO), LED85.3 (DI)
LED_DIN_85: LED85.1 (DO), LED86.3 (DI)
LED_DIN_86: LED86.1 (DO), LED87.3 (DI)
LED_DIN_87: LED87.1 (DO), LED88.3 (DI)
LED_DIN_88: LED88.1 (DO), LED89.3 (DI)
LED_DIN_89: LED89.1 (DO), LED90.3 (DI)
LED_DIN_90: LED90.1 (DO), LED91.3 (DI)
LED_DIN_91: LED91.1 (DO), LED92.3 (DI)
LED_DIN_92: LED92.1 (DO), LED93.3 (DI)
LED_DIN_93: LED93.1 (DO), LED94.3 (DI)
LED_DIN_94: LED94.1 (DO), LED95.3 (DI)
LED_DIN_95: LED95.1 (DO), LED96.3 (DI)
LED_DIN_96: LED96.1 (DO), LED97.3 (DI)
LED_DIN_97: LED97.1 (DO), LED98.3 (DI)
LED_DIN_98: LED98.1 (DO), LED99.3 (DI)
LED_DIN_99: LED99.1 (DO), LED100.3 (DI)
LED_DIN_100: LED100.1 (DO), LED101.3 (DI)
LED_DIN_101: LED101.1 (DO), LED102.3 (DI)
LED_DIN_102: LED102.1 (DO), LED103.3 (DI)
LED_DIN_103: LED103.1 (DO), LED104.3 (DI)
LED_DIN_104: LED104.1 (DO), LED105.3 (DI)
LED_DIN_105: LED105.1 (DO), LED106.3 (DI)
LED_DIN_106: LED106.1 (DO), LED107.3 (DI)
LED_DIN_107: LED107.1 (DO), LED108.3 (DI)
LED_DIN_108: LED108.1 (DO), LED109.3 (DI)
LED_DIN_109: LED109.1 (DO), LED110.3 (DI)
LED_DOUT_END: LED110.1 (DO)
PI_PWR_BUT: J5.1, Q1.3
PWR_KEY: Q1.1, R32.1, U2.40 (GPIO28/ADC2)
QSPI_SCLK: U2.52 (QSPI_SCLK), U3.6 (CLK)
QSPI_SD0: U2.53 (QSPI_SD0), U3.5 (DI(IO0))
QSPI_SD1: U2.55 (QSPI_SD1), U3.2 (DO(IO1))
QSPI_SD2: U2.54 (QSPI_SD2), U3.3 (/WP(IO2))
QSPI_SD3: U2.51 (QSPI_SD3), U3.7 (/HOLD(IO3))
QSPI_SS: R7.1, U2.56 (QSPI_SS), U3.1 (/CS)
RUN: R6.1, SW2.1, U2.26 (RUN)
SR_CLK: U2.29 (GPIO18), U4.2 (CLK), U5.2 (CLK), U6.2 (CLK)
SR_LD: U2.30 (GPIO19), U4.1 (SH/LD), U5.1 (SH/LD), U6.1 (SH/LD)
SR_Q5: U4.10 (SER), U5.9 (QH)
SR_Q6: U5.10 (SER), U6.9 (QH)
SR_QH: U2.31 (GPIO20), U4.9 (QH)
SWCLK: J4.1, U2.24 (SWCLK)
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
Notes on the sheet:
Octavio Synth - carte de facade v1 (RP2040). Genere depuis design.py : chaque broche est reliee a son net par une etiquette. Liaison interne J2 (JST-SH) : 1 GND, 2 +5V, 3 D+, 4 D-. J3 (JST-PH) : 1 +5V LED, 2 GND. JP1 : pont 0R a souder pour alimenter les LED par l'USB-C de test.
